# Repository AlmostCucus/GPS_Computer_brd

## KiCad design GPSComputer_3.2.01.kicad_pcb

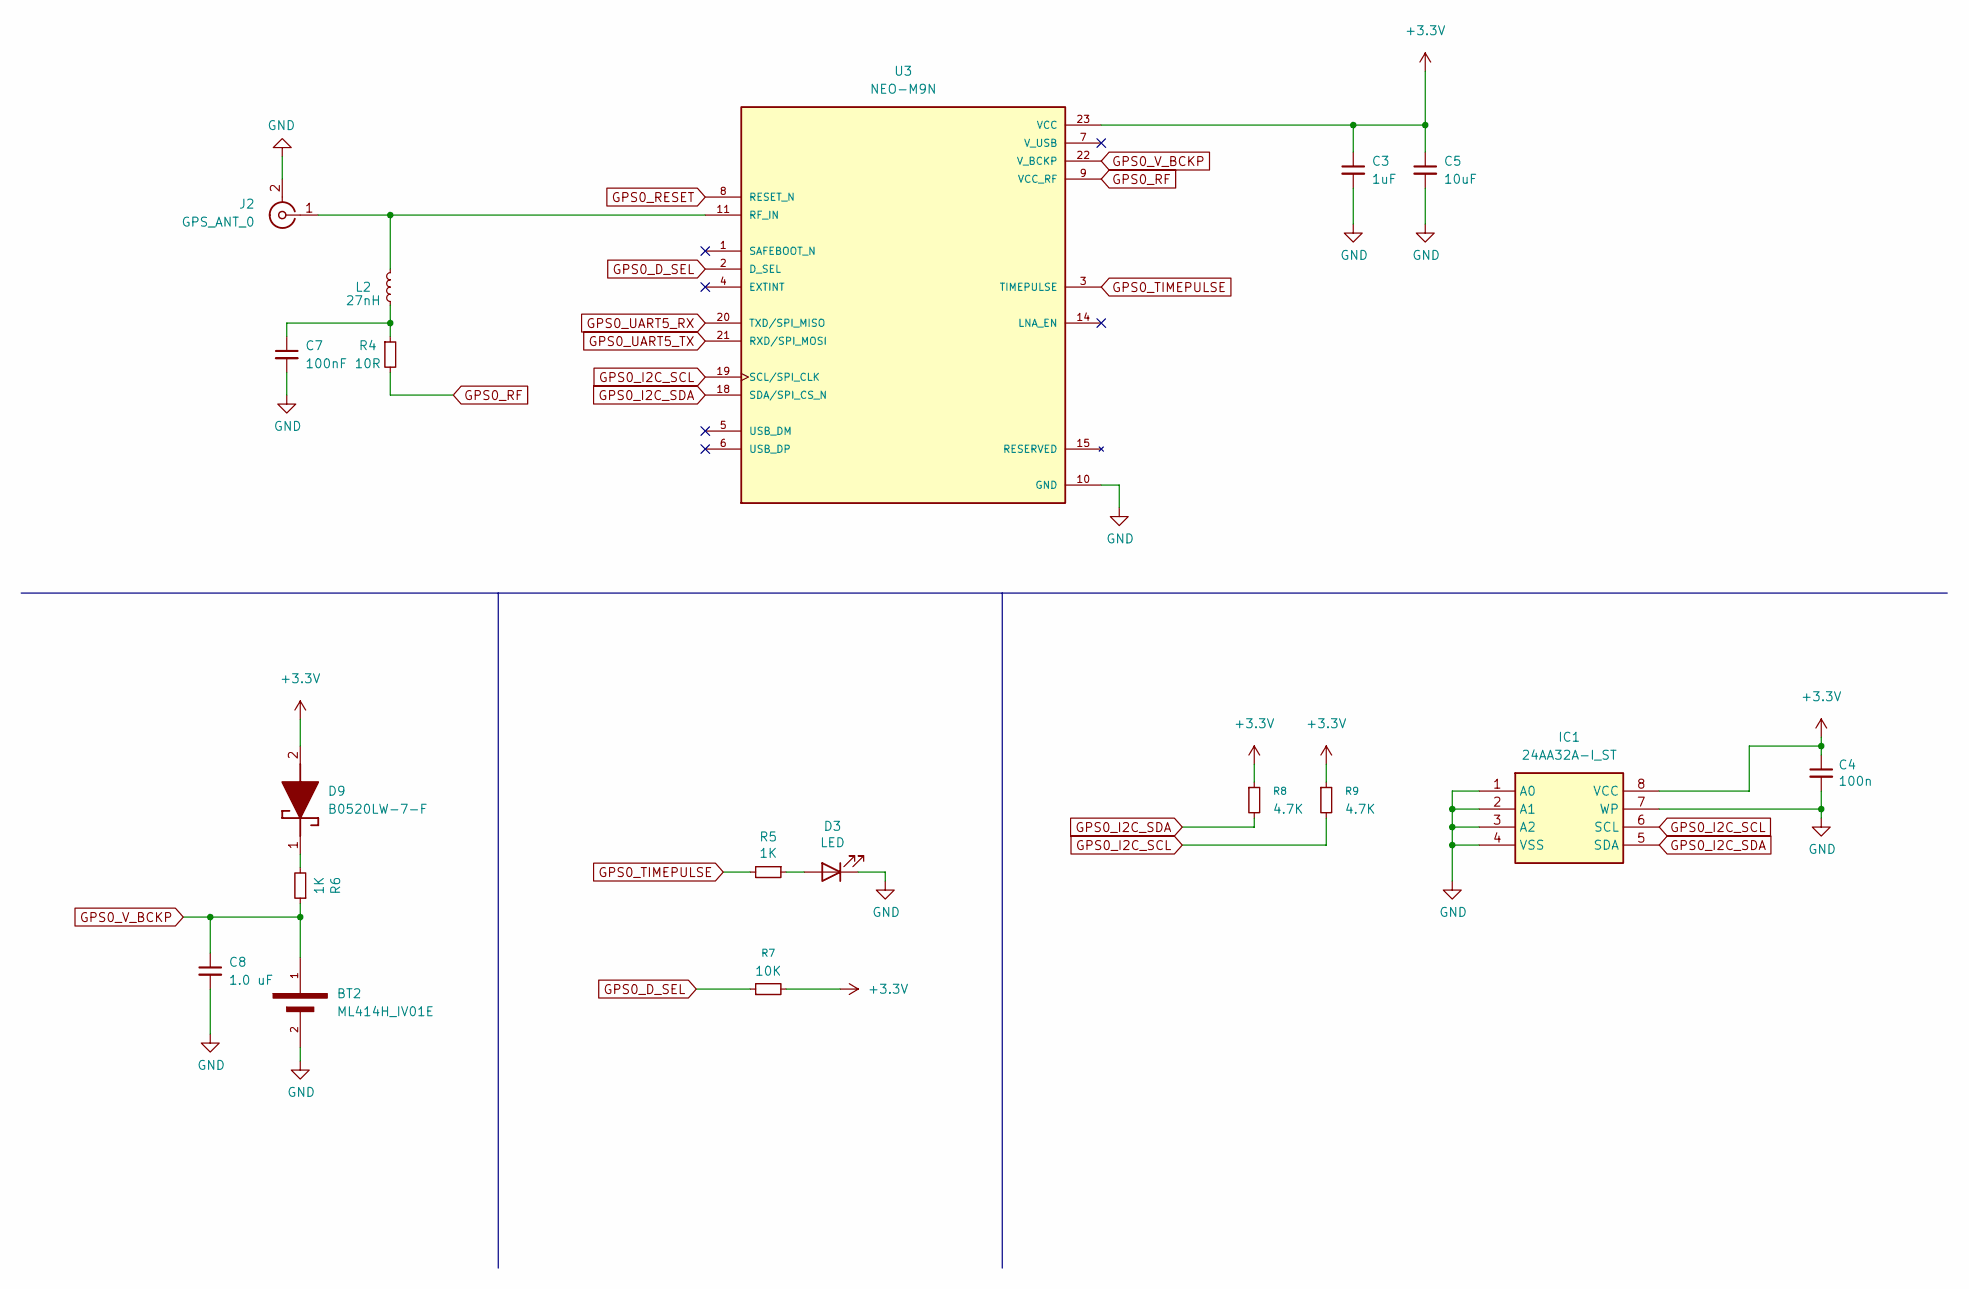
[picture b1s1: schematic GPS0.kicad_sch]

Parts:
BT2: ML414H_IV01E; SEIKO_ML414H_IV01E
C3: 1uF; C_1210_3225Metric
C4: 100n; C_0402_1005Metric
C5: 10uF; C_1210_3225Metric
C7: 100nF; C_0402_1005Metric
C8: 1.0 uF; C_0805_2012Metric
D3: LED; LED_0805_2012Metric_Pad1.15x1.40mm_HandSolder
D9: B0520LW-7-F; SOD3716X145N; Manufacturer_Part_Number B0520LW-7-F; Mouser Part Number 621-B0520LW-F
IC1: 24AA32A-I_ST; SOP65P640X120-8N; Manufacturer_Part_Number 24AA32A-I/ST; Mouser Part Number 579-24AA32A-I/ST
J2: GPS_ANT_0; SMA_Samtec_SMA-J-P-H-ST-EM1_EdgeMount
L2: 27nH; L_0402_1005Metric
R4: 10R; R_0402_1005Metric
R5, R6: 1K; R_0805_2012Metric
R7: 10K; R_0402_1005Metric
R8, R9: 4.7K; R_0402_1005Metric
U3: NEO-M9N; XCVR_NEO-M9N; PARTREV R05

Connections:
+3.3V: C3.1, C4.1, C5.1, D9.2 (A), IC1.8 (VCC), R7.2, R8.1, R9.1, U3.23 (VCC); also elsewhere on the board
GND: BT2.2, C3.2, C4.2, C5.2, C7.2, C8.2, D3.1 (K), IC1.1 (A0), IC1.2 (A1), IC1.3 (A2), IC1.4 (VSS), IC1.7 (WP), J2.2 (Ext), U3.10 (GND), U3.12 (GND), U3.13 (GND), U3.24 (GND); also elsewhere on the board
GPS0_D_SEL: R7.1, U3.2 (D_SEL)
GPS0_I2C_SCL: IC1.6 (SCL), R9.2, U3.19 (SCL/SPI_CLK)
GPS0_I2C_SDA: IC1.5 (SDA), R8.2, U3.18 (SDA/SPI_CS_N)
GPS0_RESET: U3.8 (RESET_N); also elsewhere on the board
GPS0_RF: R4.2, U3.9 (VCC_RF)
GPS0_TIMEPULSE: R5.2, U3.3 (TIMEPULSE)
GPS0_UART5_RX: U3.20 (TXD/SPI_MISO); also elsewhere on the board
GPS0_UART5_TX: U3.21 (RXD/SPI_MOSI); also elsewhere on the board
GPS0_V_BCKP: BT2.1, C8.1, R6.1, U3.22 (V_BCKP)
unnamed: C7.1, L2.1, R4.1
unnamed: D3.2 (A), R5.1
unnamed: D9.1 (K), R6.2
unnamed: J2.1 (In), L2.2, U3.11 (RF_IN)

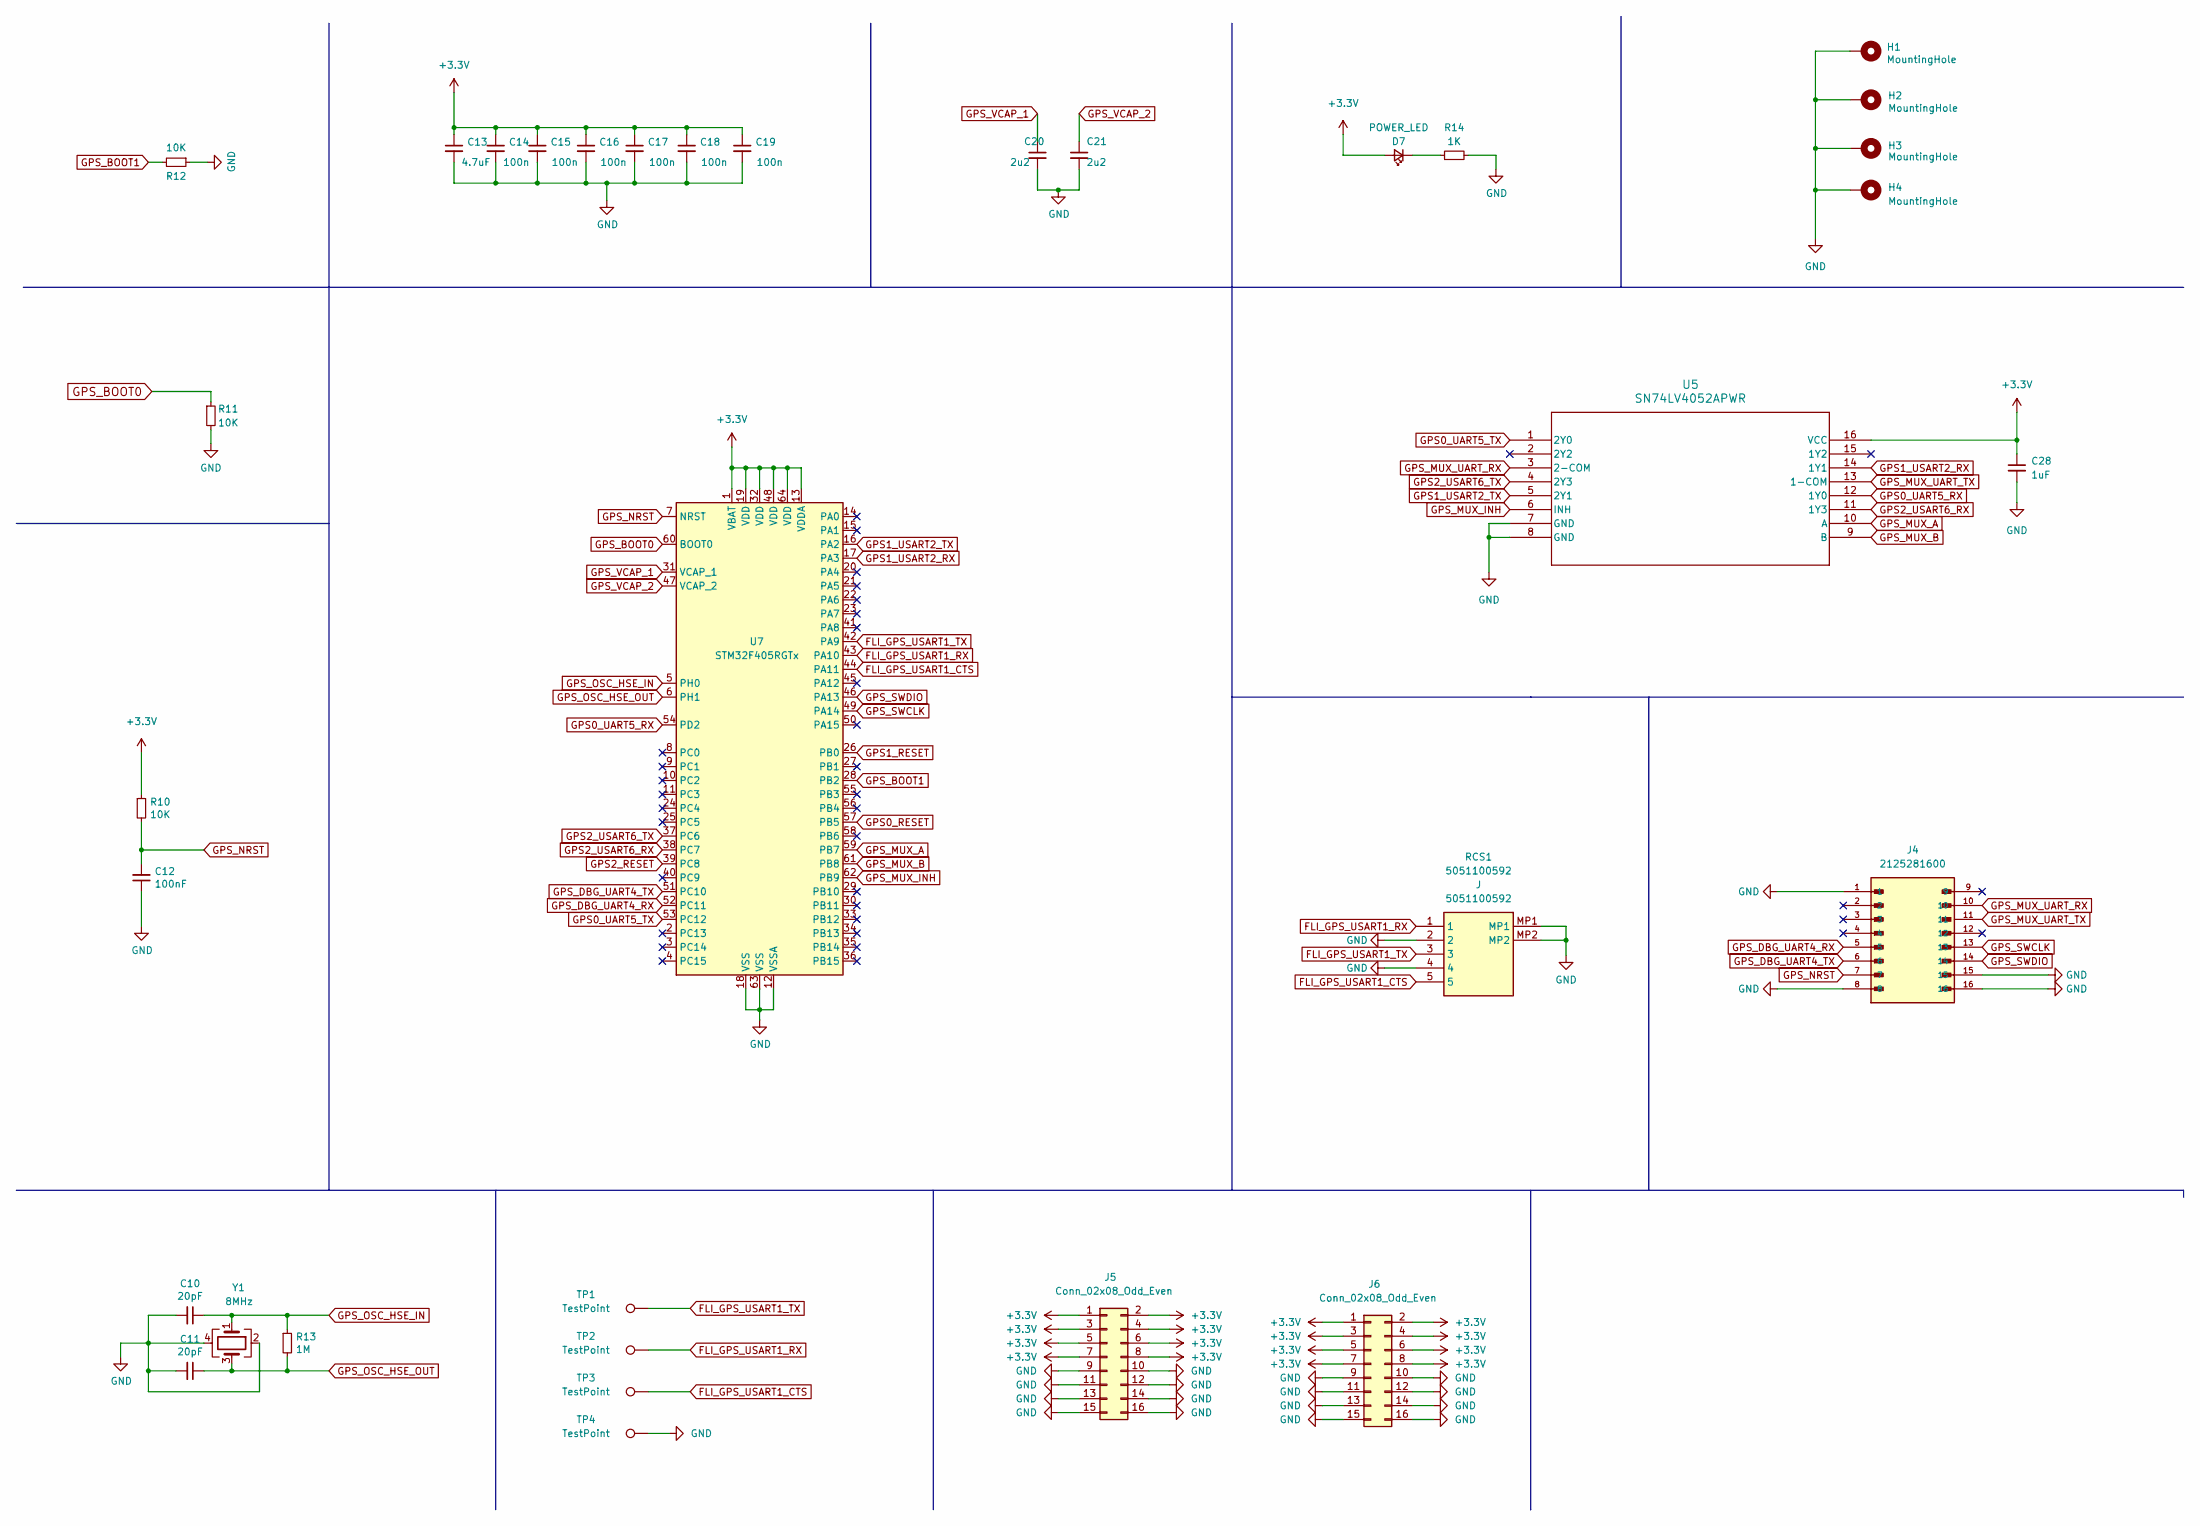
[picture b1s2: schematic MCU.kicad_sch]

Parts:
C10, C11: 20pF; C_0402_1005Metric
C12: 100nF; C_0402_1005Metric
C13: 4.7uF; C_0402_1005Metric
C14, C15, C16, C17, C18, C19: 100n; C_0402_1005Metric
C20, C21: 2u2; C_0603_1608Metric
C28: 1uF; C_0402_1005Metric
D7: POWER_LED; LED_0603_1608Metric
H1, H2, H3, H4: MountingHole; MountingHole_3.2mm_M3_Pad_Via
J4: 2125281600; MOLEX_2125281600; PARTREV A3
J5: Conn_02x08_Odd_Even; PinHeader_2x08_P2.54mm_Vertical_SMD
J6: Conn_02x08_Odd_Even; PinSocket_2x08_P2.54mm_Vertical_SMD
R10, R11, R12: 10K; R_0402_1005Metric
R13: 1M; R_0402_1005Metric
R14: 1K; R_0402_1005Metric
RCS1: 5051100592; Manufacturer_Part_Number 5051100592; Mouser Part Number N/A
TP1, TP2, TP3, TP4: TestPoint; TestPoint_Pad_D1.0mm
U5: SN74LV4052APWR; PW16
U7: STM32F405RGTx; LQFP-64_10x10mm_P0.5mm
Y1: 8MHz; Crystal_SMD_5032-4Pin_5.0x3.2mm

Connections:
+3.3V: C13.1, C14.1, C15.1, C16.1, C17.1, C18.1, C19.1, C28.1, D7.2 (A), J5.1, J5.2, J5.3, J5.4, J5.5, J5.6, J5.7, J5.8, J6.1, J6.2, J6.3, J6.4, J6.5, J6.6, J6.7, J6.8, R10.1, U5.16 (VCC), U7.1 (VBAT), U7.13 (VDDA), U7.19 (VDD), U7.32 (VDD), U7.48 (VDD), U7.64 (VDD); also elsewhere on the board
FLI_GPS_USART1_CTS: RCS1.5, TP3.1, U7.44 (PA11)
FLI_GPS_USART1_RX: RCS1.1, TP2.1, U7.43 (PA10)
FLI_GPS_USART1_TX: RCS1.3, TP1.1, U7.42 (PA9)
GND: C10.2, C11.2, C12.1, C13.2, C14.2, C15.2, C16.2, C17.2, C18.2, C19.2, C20.2, C21.2, C28.2, H1.1, H2.1, H3.1, H4.1, J4.1, J4.8, J4.15, J4.16, J5.9, J5.10, J5.11, J5.12, J5.13, J5.14, J5.15, J5.16, J6.9, J6.10, J6.11, J6.12, J6.13, J6.14, J6.15, J6.16, R11.2, R12.1, R14.2, RCS1.2, RCS1.4, RCS1.MP1, RCS1.MP2, TP4.1, U5.7 (GND), U5.8 (GND), U7.12 (VSSA), U7.18 (VSS), U7.63 (VSS), Y1.2, Y1.4; also elsewhere on the board
GPS0_RESET: U7.57 (PB5); also elsewhere on the board
GPS0_UART5_RX: U5.12 (1Y0), U7.54 (PD2); also elsewhere on the board
GPS0_UART5_TX: U5.1 (2Y0), U7.53 (PC12); also elsewhere on the board
GPS1_RESET: U7.26 (PB0); also elsewhere on the board
GPS1_USART2_RX: U5.14 (1Y1), U7.17 (PA3); also elsewhere on the board
GPS1_USART2_TX: U5.5 (2Y1), U7.16 (PA2); also elsewhere on the board
GPS2_RESET: U7.39 (PC8); also elsewhere on the board
GPS2_USART6_RX: U5.11 (1Y3), U7.38 (PC7); also elsewhere on the board
GPS2_USART6_TX: U5.4 (2Y3), U7.37 (PC6); also elsewhere on the board
GPS_BOOT0: R11.1, U7.60 (BOOT0)
GPS_BOOT1: R12.2, U7.28 (PB2)
GPS_DBG_UART4_RX: J4.5, U7.52 (PC11)
GPS_DBG_UART4_TX: J4.6, U7.51 (PC10)
GPS_MUX_A: U5.10 (A), U7.59 (PB7)
GPS_MUX_B: U5.9 (B), U7.61 (PB8)
GPS_MUX_INH: U5.6 (INH), U7.62 (PB9)
GPS_MUX_UART_RX: J4.10, U5.3 (2-COM)
GPS_MUX_UART_TX: J4.11, U5.13 (1-COM)
GPS_NRST: C12.2, J4.7, R10.2, U7.7 (NRST)
GPS_OSC_HSE_IN: C10.1, R13.1, U7.5 (PH0), Y1.1
GPS_OSC_HSE_OUT: C11.1, R13.2, U7.6 (PH1), Y1.3
GPS_SWCLK: J4.13, U7.49 (PA14)
GPS_SWDIO: J4.14, U7.46 (PA13)
GPS_VCAP_1: C20.1, U7.31 (VCAP_1)
GPS_VCAP_2: C21.1, U7.47 (VCAP_2)
unnamed: D7.1 (K), R14.1

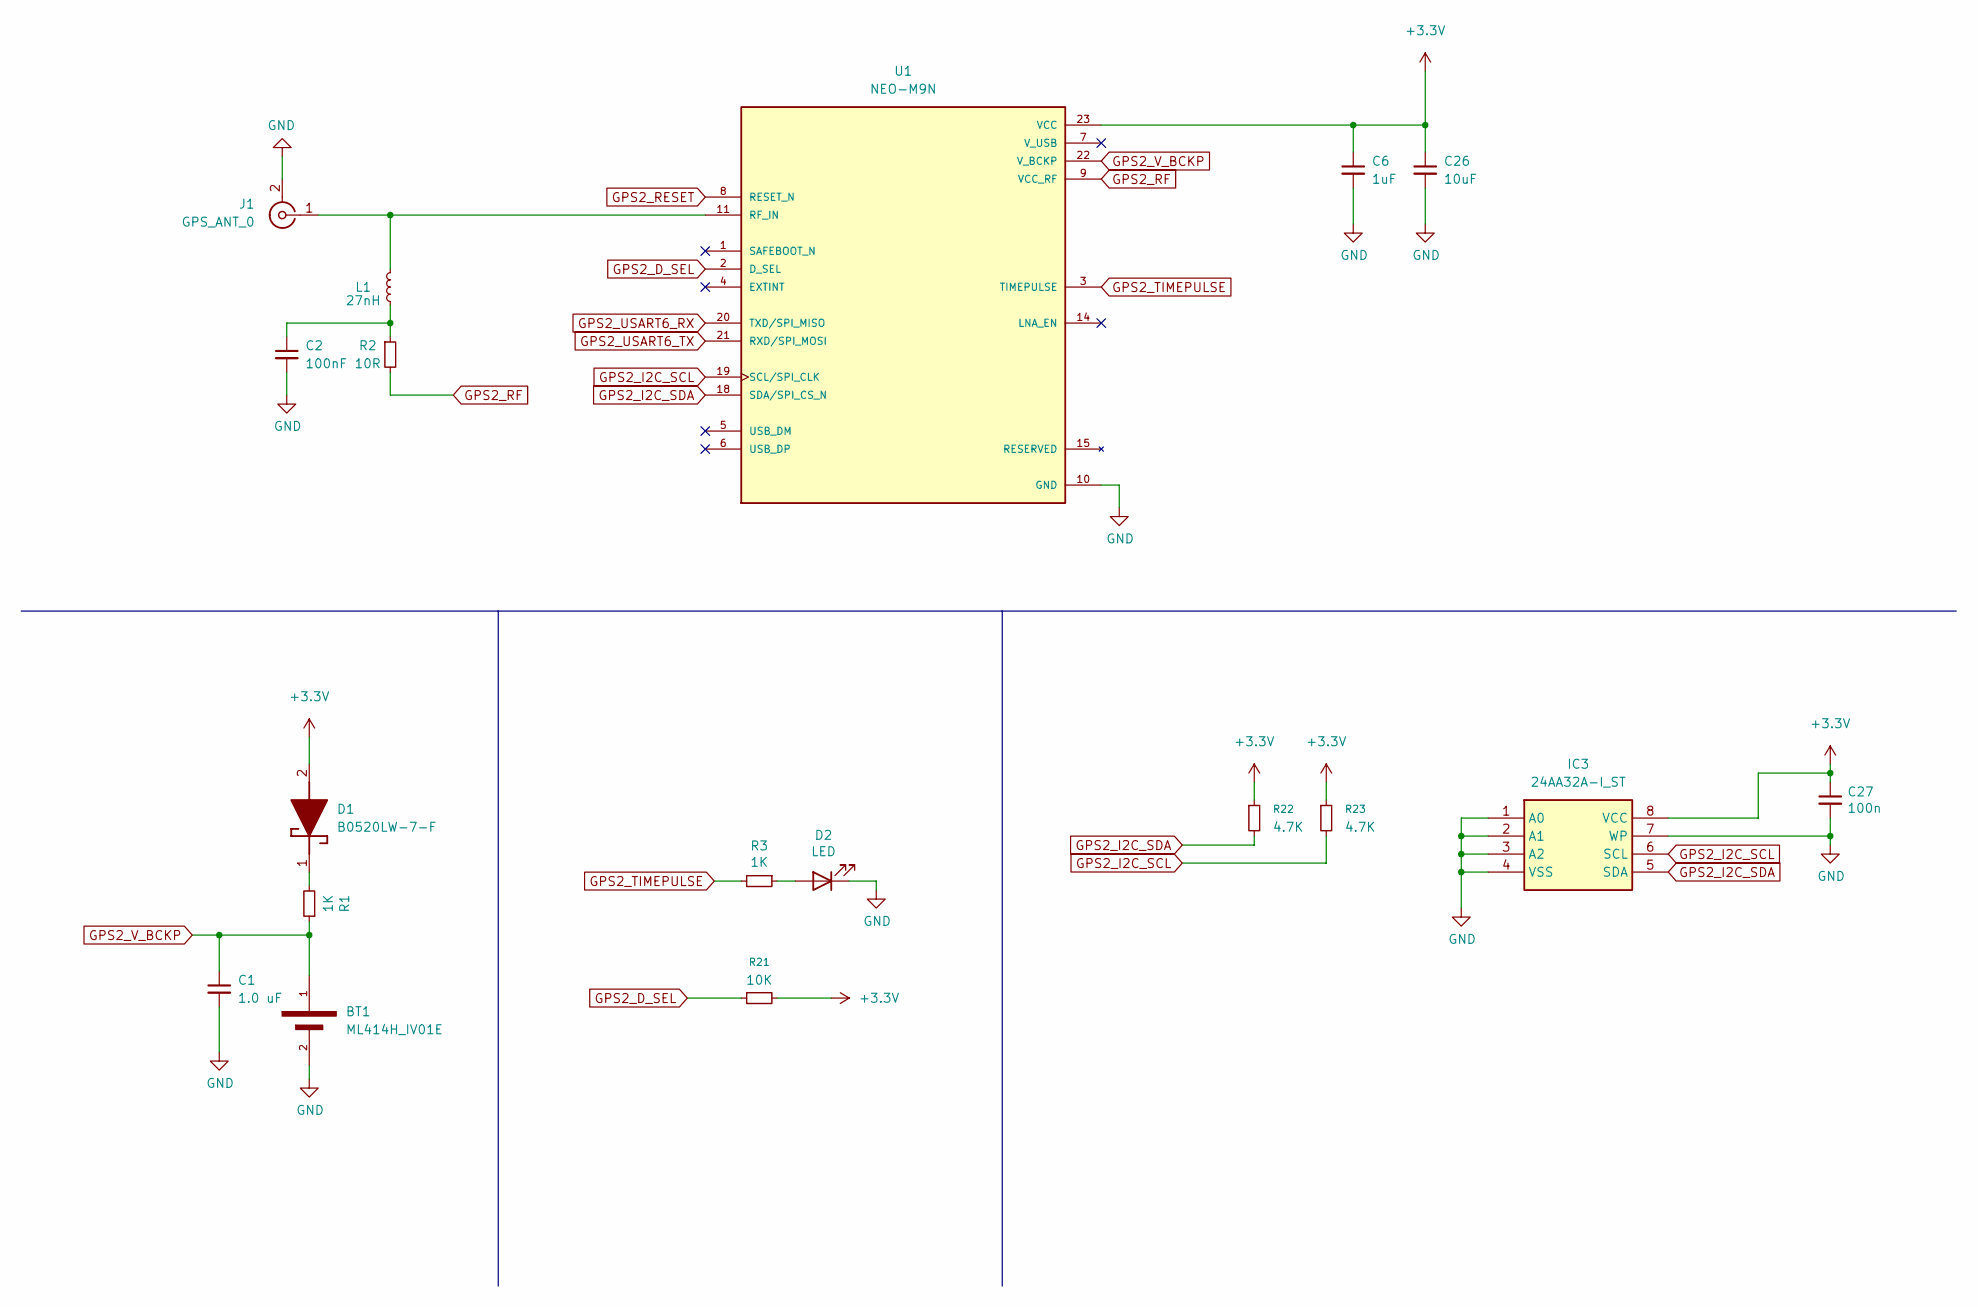
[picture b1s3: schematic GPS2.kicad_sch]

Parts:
BT1: ML414H_IV01E; SEIKO_ML414H_IV01E
C1: 1.0 uF; C_0805_2012Metric
C2: 100nF; C_0402_1005Metric
C6: 1uF; C_1210_3225Metric
C26: 10uF; C_1210_3225Metric
C27: 100n; C_0402_1005Metric
D1: B0520LW-7-F; SOD3716X145N; Manufacturer_Part_Number B0520LW-7-F; Mouser Part Number 621-B0520LW-F
D2: LED; LED_0805_2012Metric_Pad1.15x1.40mm_HandSolder
IC3: 24AA32A-I_ST; SOP65P640X120-8N; Manufacturer_Part_Number 24AA32A-I/ST; Mouser Part Number 579-24AA32A-I/ST
J1: GPS_ANT_0; SMA_Samtec_SMA-J-P-H-ST-EM1_EdgeMount
L1: 27nH; L_0402_1005Metric
R1, R3: 1K; R_0805_2012Metric
R2: 10R; R_0402_1005Metric
R21: 10K; R_0402_1005Metric
R22, R23: 4.7K; R_0402_1005Metric
U1: NEO-M9N; XCVR_NEO-M9N; PARTREV R05

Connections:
+3.3V: C6.1, C26.1, C27.1, D1.2 (A), IC3.8 (VCC), R21.2, R22.1, R23.1, U1.23 (VCC); also elsewhere on the board
GND: BT1.2, C1.2, C2.2, C6.2, C26.2, C27.2, D2.1 (K), IC3.1 (A0), IC3.2 (A1), IC3.3 (A2), IC3.4 (VSS), IC3.7 (WP), J1.2 (Ext), U1.10 (GND), U1.12 (GND), U1.13 (GND), U1.24 (GND); also elsewhere on the board
GPS2_D_SEL: R21.1, U1.2 (D_SEL)
GPS2_I2C_SCL: IC3.6 (SCL), R23.2, U1.19 (SCL/SPI_CLK)
GPS2_I2C_SDA: IC3.5 (SDA), R22.2, U1.18 (SDA/SPI_CS_N)
GPS2_RESET: U1.8 (RESET_N); also elsewhere on the board
GPS2_RF: R2.2, U1.9 (VCC_RF)
GPS2_TIMEPULSE: R3.2, U1.3 (TIMEPULSE)
GPS2_USART6_RX: U1.20 (TXD/SPI_MISO); also elsewhere on the board
GPS2_USART6_TX: U1.21 (RXD/SPI_MOSI); also elsewhere on the board
GPS2_V_BCKP: BT1.1, C1.1, R1.1, U1.22 (V_BCKP)
unnamed: C2.1, L1.1, R2.1
unnamed: D1.1 (K), R1.2
unnamed: D2.2 (A), R3.1
unnamed: J1.1 (In), L1.2, U1.11 (RF_IN)

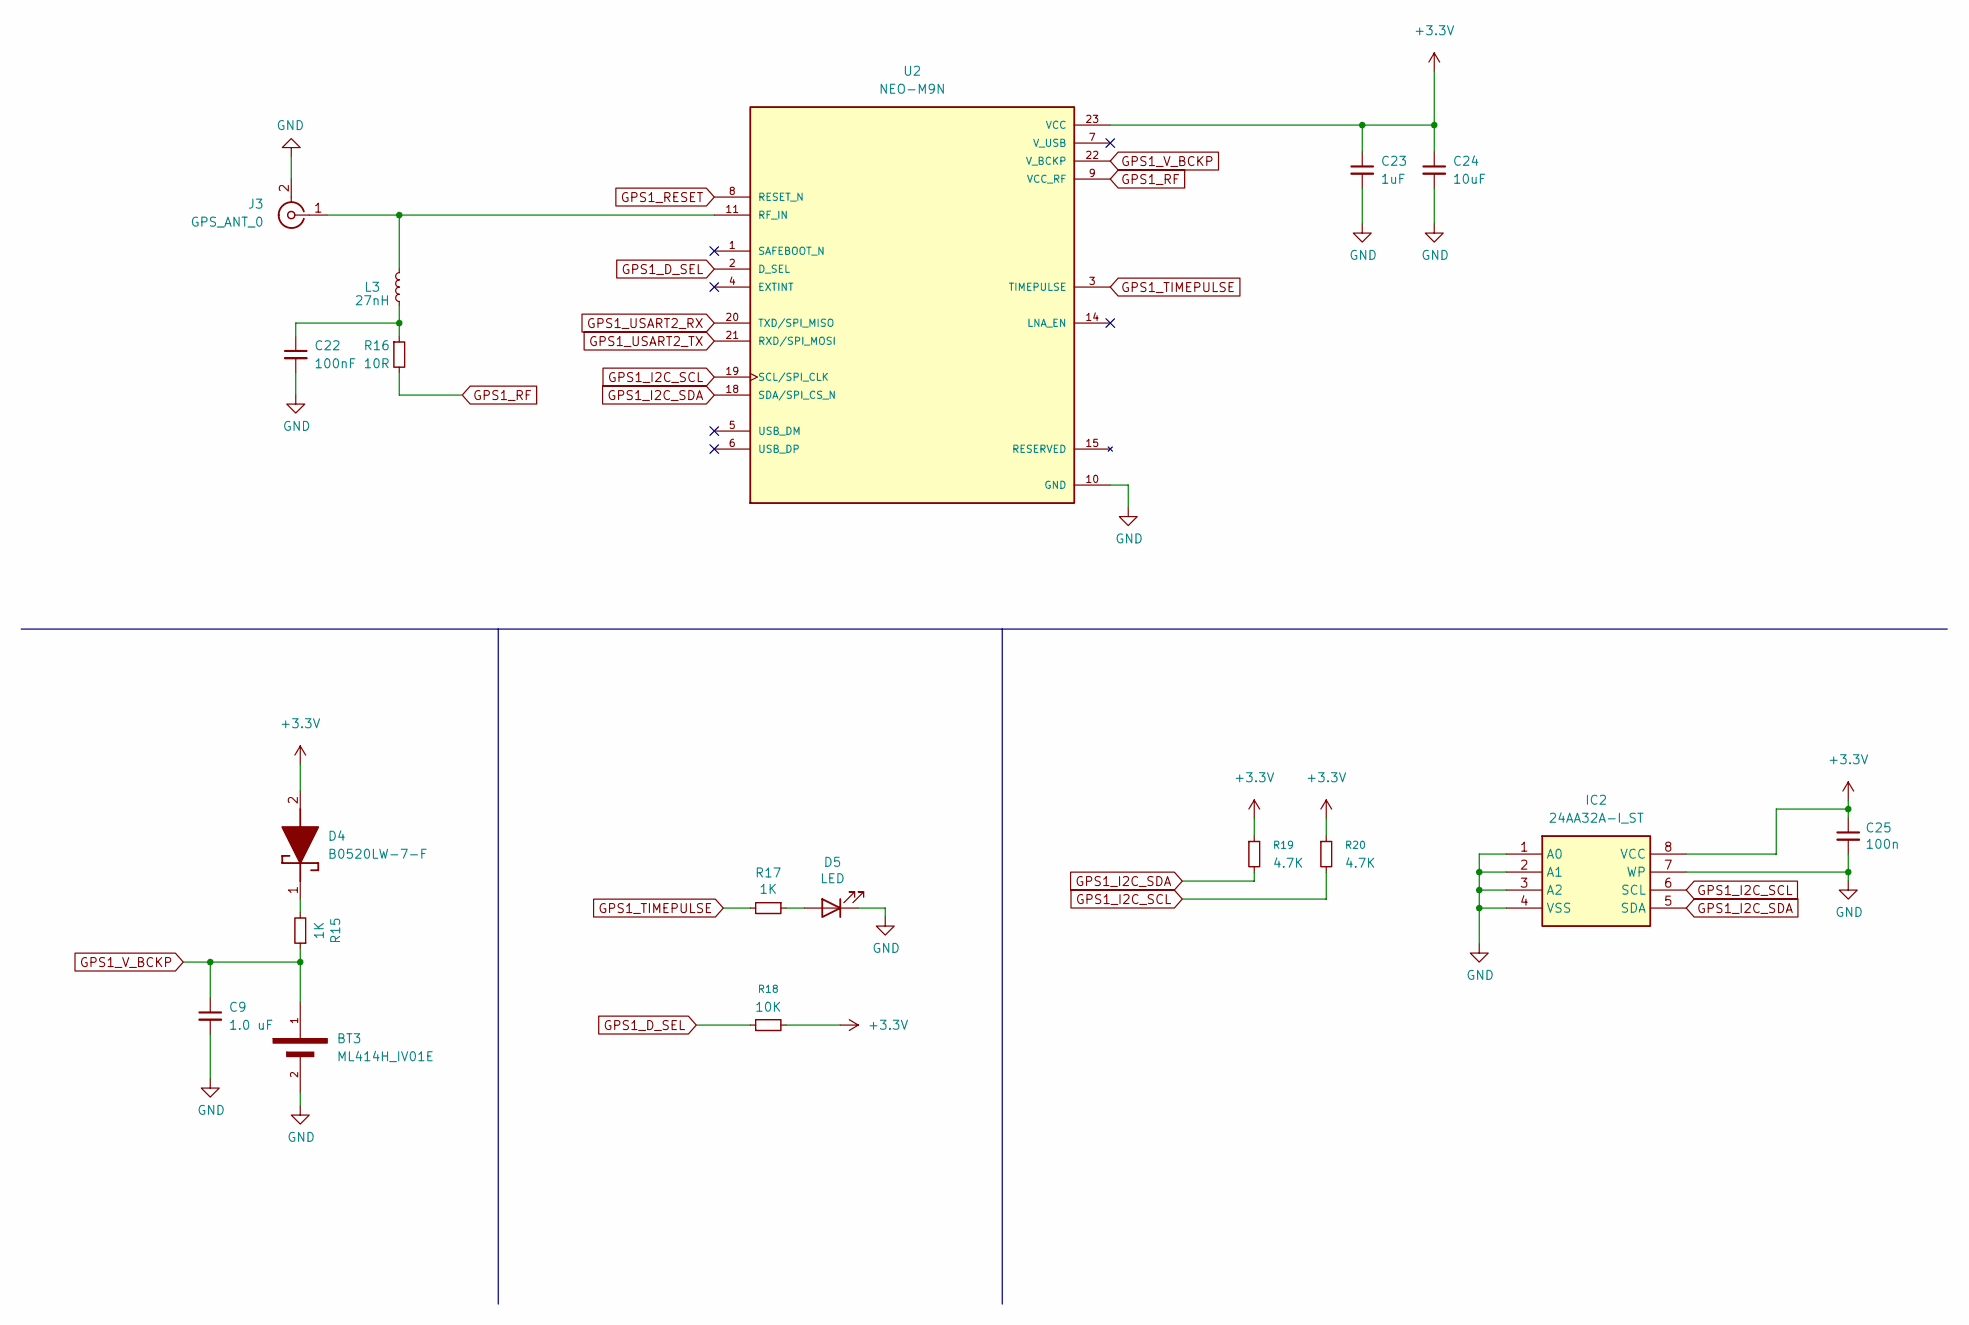
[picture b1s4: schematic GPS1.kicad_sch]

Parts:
BT3: ML414H_IV01E; SEIKO_ML414H_IV01E
C9: 1.0 uF; C_0805_2012Metric
C22: 100nF; C_0402_1005Metric
C23: 1uF; C_1210_3225Metric
C24: 10uF; C_1210_3225Metric
C25: 100n; C_0402_1005Metric
D4: B0520LW-7-F; SOD3716X145N; Manufacturer_Part_Number B0520LW-7-F; Mouser Part Number 621-B0520LW-F
D5: LED; LED_0805_2012Metric_Pad1.15x1.40mm_HandSolder
IC2: 24AA32A-I_ST; SOP65P640X120-8N; Manufacturer_Part_Number 24AA32A-I/ST; Mouser Part Number 579-24AA32A-I/ST
J3: GPS_ANT_0; SMA_Samtec_SMA-J-P-H-ST-EM1_EdgeMount
L3: 27nH; L_0402_1005Metric
R15, R17: 1K; R_0805_2012Metric
R16: 10R; R_0402_1005Metric
R18: 10K; R_0402_1005Metric
R19, R20: 4.7K; R_0402_1005Metric
U2: NEO-M9N; XCVR_NEO-M9N; PARTREV R05

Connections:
+3.3V: C23.1, C24.1, C25.1, D4.2 (A), IC2.8 (VCC), R18.2, R19.1, R20.1, U2.23 (VCC); also elsewhere on the board
GND: BT3.2, C9.2, C22.2, C23.2, C24.2, C25.2, D5.1 (K), IC2.1 (A0), IC2.2 (A1), IC2.3 (A2), IC2.4 (VSS), IC2.7 (WP), J3.2 (Ext), U2.10 (GND), U2.12 (GND), U2.13 (GND), U2.24 (GND); also elsewhere on the board
GPS1_D_SEL: R18.1, U2.2 (D_SEL)
GPS1_I2C_SCL: IC2.6 (SCL), R20.2, U2.19 (SCL/SPI_CLK)
GPS1_I2C_SDA: IC2.5 (SDA), R19.2, U2.18 (SDA/SPI_CS_N)
GPS1_RESET: U2.8 (RESET_N); also elsewhere on the board
GPS1_RF: R16.2, U2.9 (VCC_RF)
GPS1_TIMEPULSE: R17.2, U2.3 (TIMEPULSE)
GPS1_USART2_RX: U2.20 (TXD/SPI_MISO); also elsewhere on the board
GPS1_USART2_TX: U2.21 (RXD/SPI_MOSI); also elsewhere on the board
GPS1_V_BCKP: BT3.1, C9.1, R15.1, U2.22 (V_BCKP)
unnamed: C22.1, L3.1, R16.1
unnamed: D4.1 (K), R15.2
unnamed: D5.2 (A), R17.1
unnamed: J3.1 (In), L3.2, U2.11 (RF_IN)

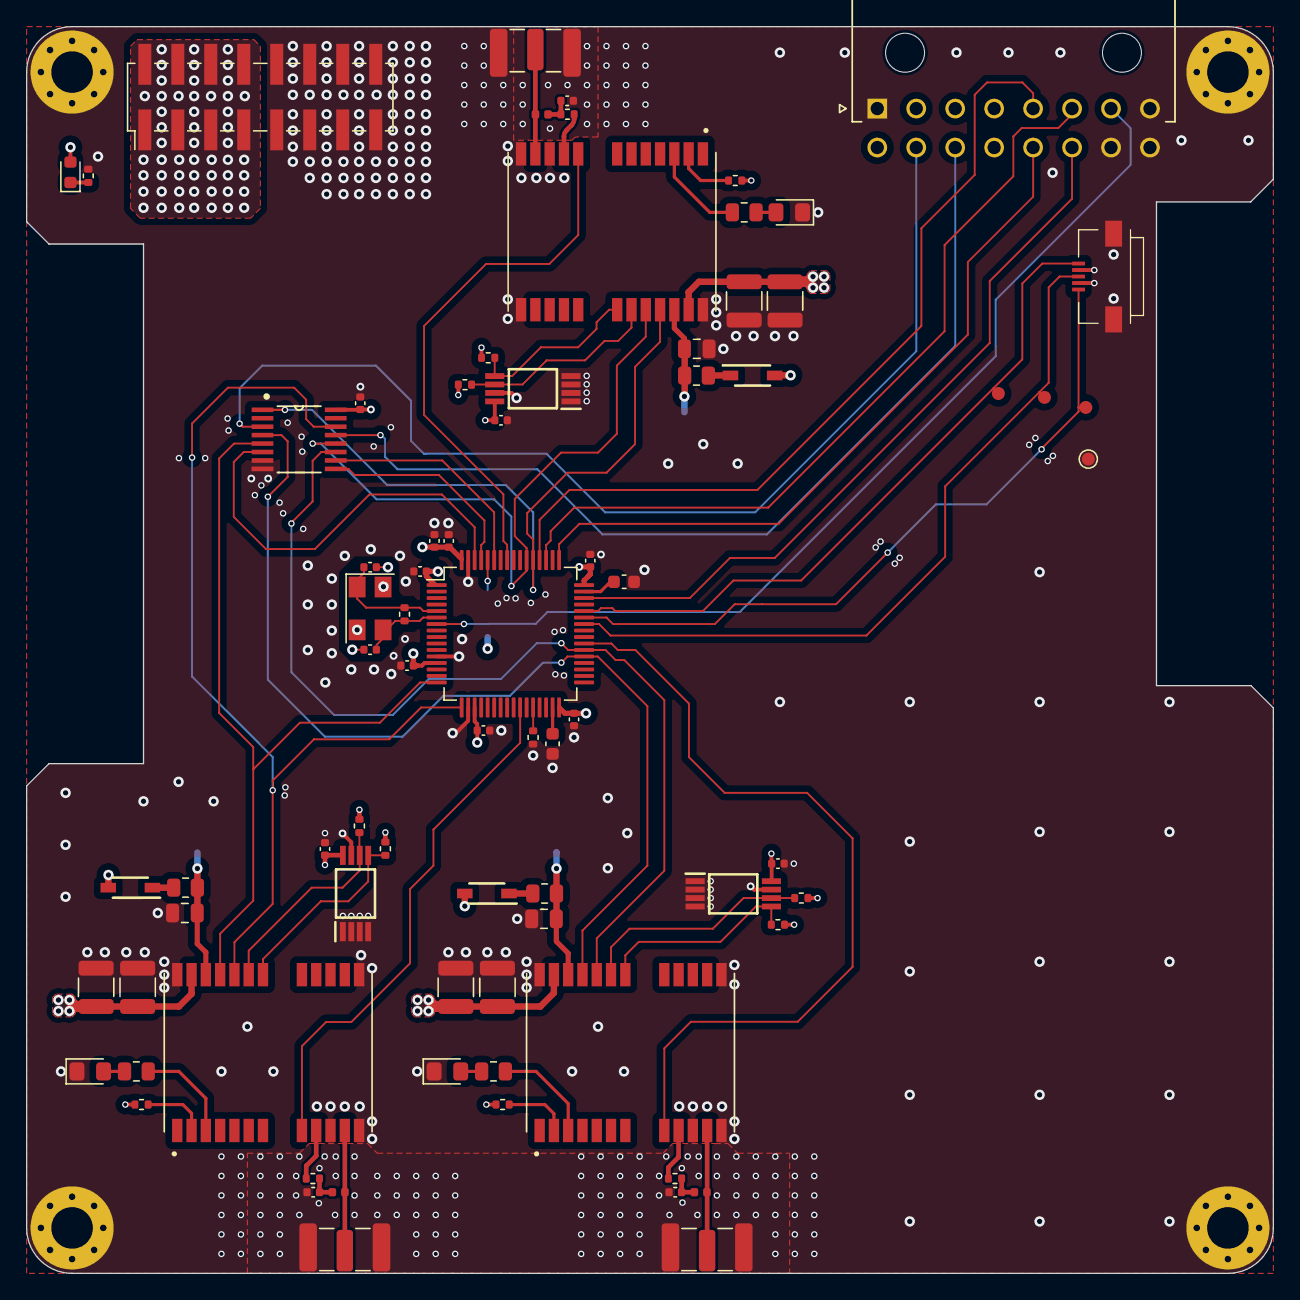
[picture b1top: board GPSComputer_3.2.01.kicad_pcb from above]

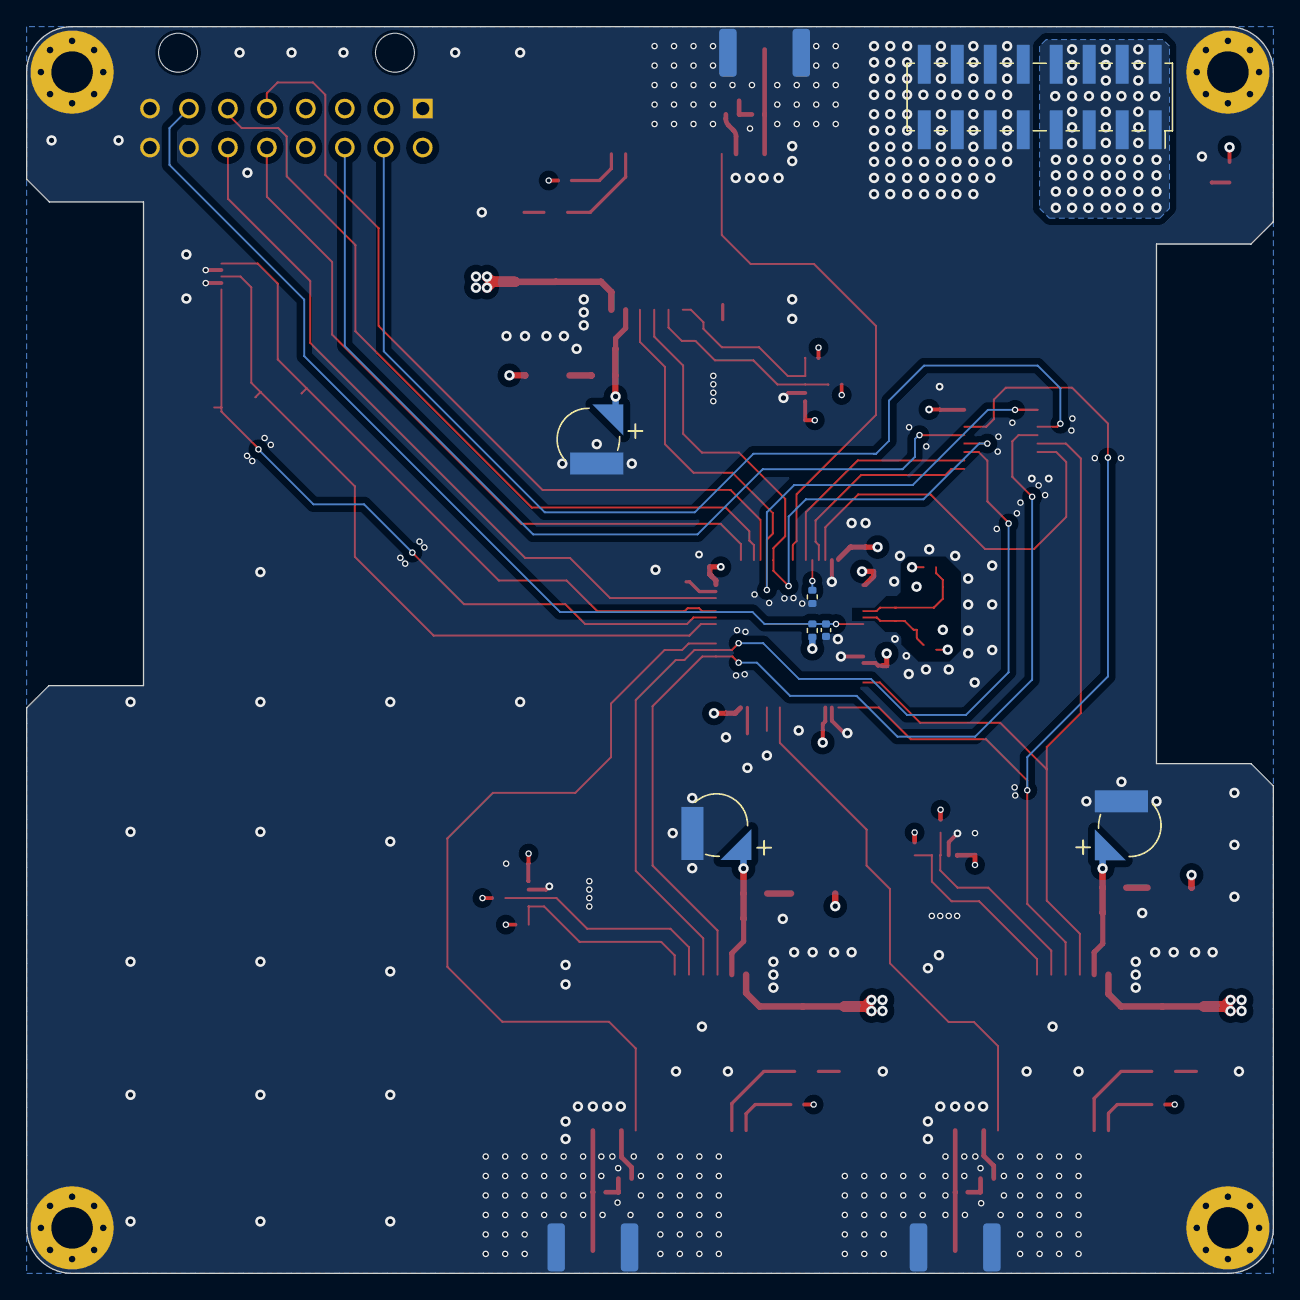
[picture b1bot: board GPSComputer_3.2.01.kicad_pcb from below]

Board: 4 copper layers, 96.0 x 96.0 mm, 88 parts (7 on the bottom side), 61 nets.

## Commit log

2025-06-18 MAX-M10S-00B
2025-06-18 Adding M10
2025-06-19 Finished M10
2025-06-19 Adding RF
2025-06-20 Corrected battery position
2026-03-03 Last commit
2026-03-08 Second commit
2026-04-12 Correcet MUX pins
